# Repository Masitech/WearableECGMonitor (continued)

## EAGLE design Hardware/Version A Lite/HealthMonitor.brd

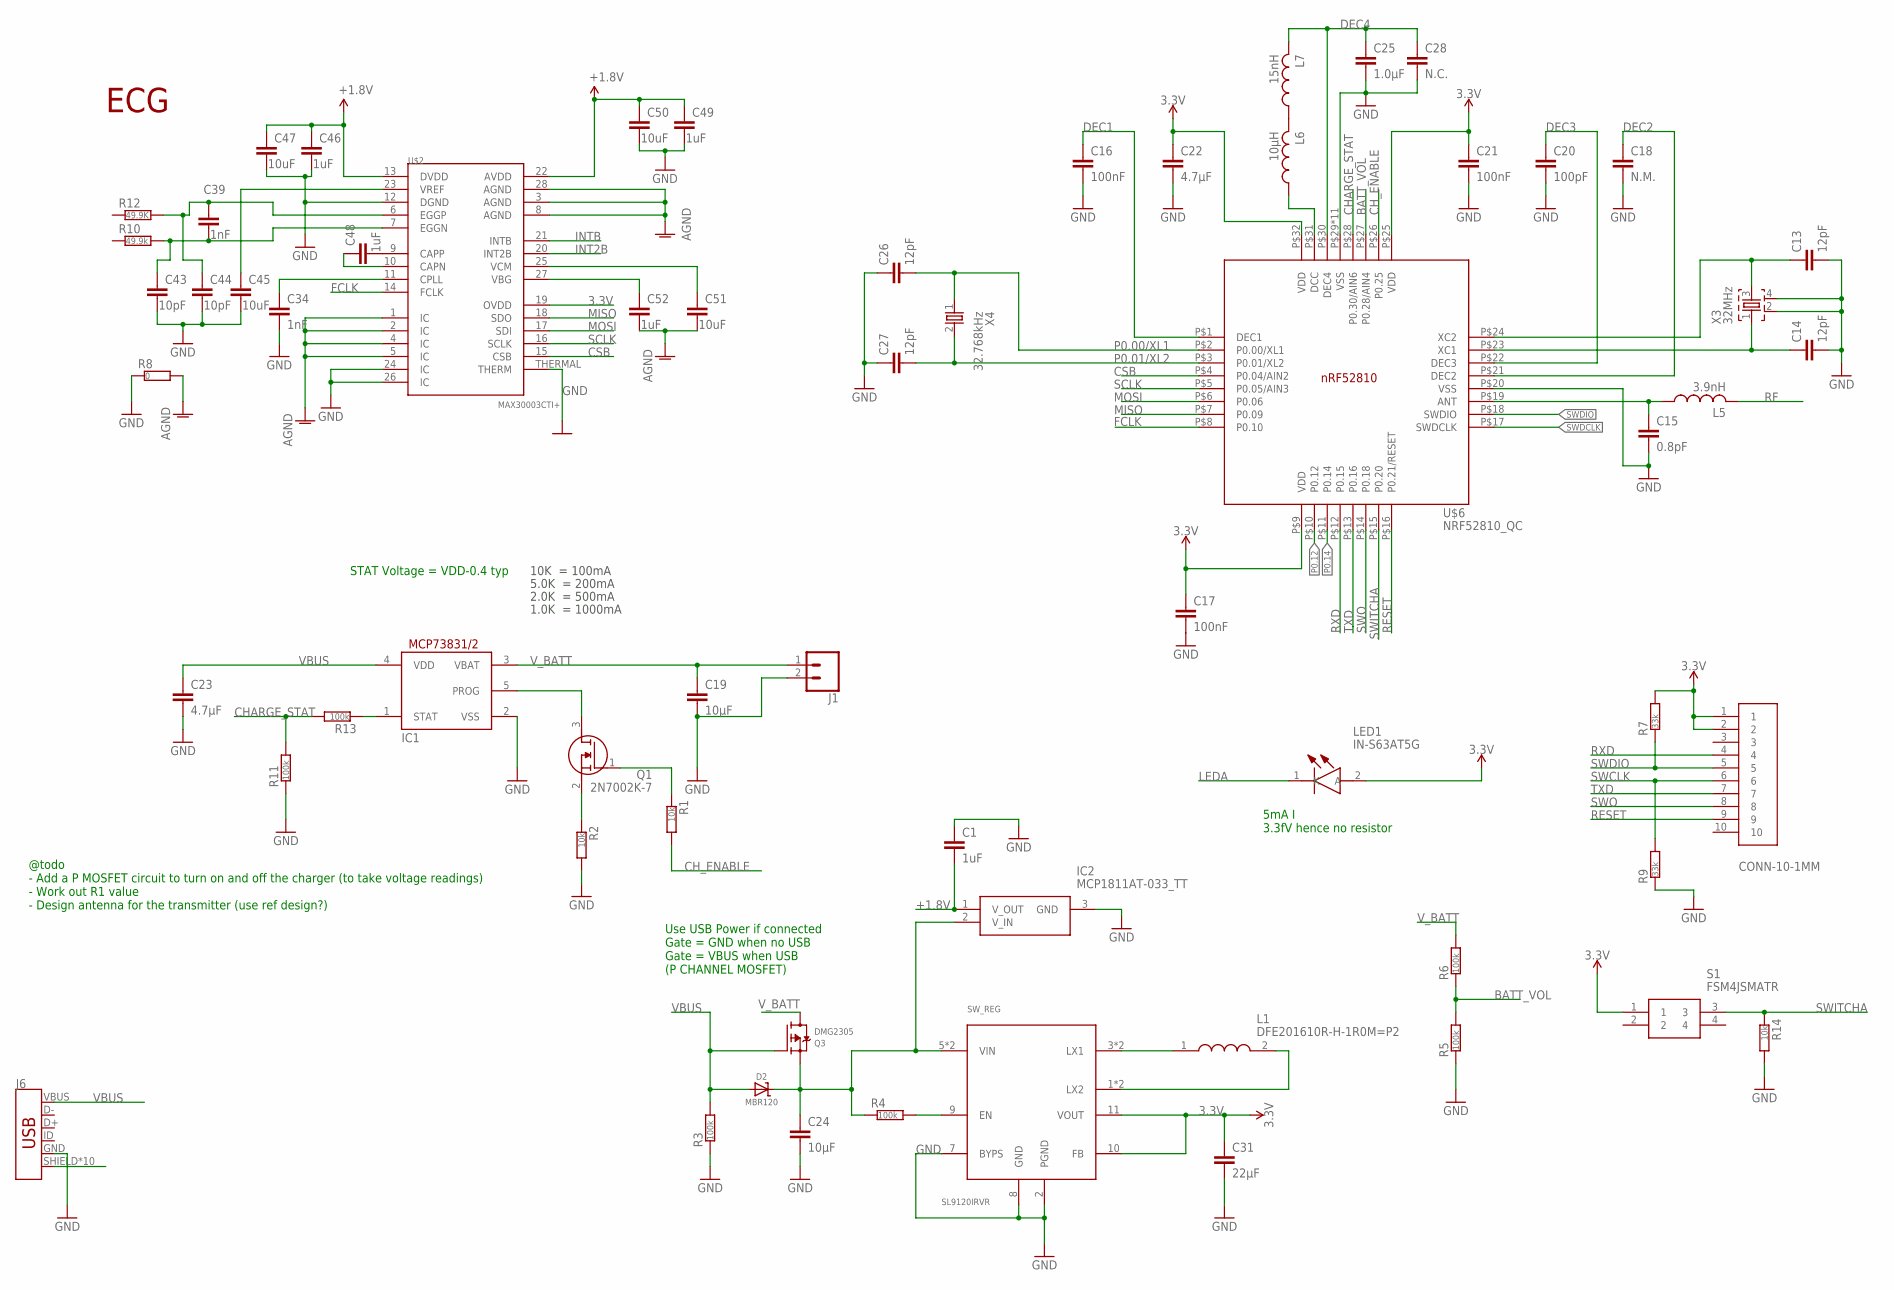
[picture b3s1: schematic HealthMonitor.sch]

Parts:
C1: 1uF; RESC0402_N
C13, C14, C26, C27: 12pF; RESC0402_N
C15: 0.8pF; RESC0402_N
C16, C17, C21: 100nF; RESC0402_N
C18: N.M.; RESC0402_N
C19, C24: 10µF; RESC0603_N
C20: 100pF; RESC0402_N
C22, C23: 4.7µF; RESC0603_N
C25: 1.0µF; RESC0603_N
C28: N.C.; RESC0402_N
C31: 22µF; RESC0603_N
C34: 1nF; C0805
C39: 1nF; RESC0603_N
C43, C44: 10pF; RESC0603_N
C45, C47, C50, C51: 10uF; RESC0603_N
C46, C48, C49, C52: 1uF; RESC0603_N
D2: MBR120; SOD-123
IC1: MCP73831/OT; SOT23-5L
IC2: MCP1811AT-033_TT; SOT95P237X112-3N
J1: CONN_02; 1X02
J6: USB_MICRO-B_HALF_PTH_MILL; USB-MICROB-PTH-MILL
L1: DFE201610R-H-1R0M=P2; INDC2016X100N
L5: 3.9nH; RESC0402_N
L6: 10µH; RESC0603_N
L7: 15nH; RESC0402_N
LED1: IN-S63AT5G; LEDM168X39N
Q1: 2N7002K-7; SOT96P240X100-3N
Q3: DMG2305; SOT23-R
R1, R2, R14: 10k; RESC0402_N
R3, R4, R5, R6, R11, R13: 100k; RESC0402_N
R7, R9: 33k; RESC0402_N
R8: 0; RESC0402_N
R10: 49.9k; RESC0402_N
R12: 49.9K; RESC0402_N
S1: FSM4JSMATR
SW_REG: SL9120IRVR; TQFN-12
U$1: CONN-10-1MM
U$2: MAX30003CTI+; QFN-28
U$6: NRF52810_QC; QFN50P500X500X90-32_N
X3: 32MHz; BT-XTAL_2016_N
X4: 32.768kHz; XTAL_3215_N

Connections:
3.3V: C17.1, C21.1, C22.1, C31.1, LED1.2 (A), R7.2, S1.1, SW_REG.10 (FB), SW_REG.11 (VOUT), U$1.1, U$1.2, U$2.19 (OVDD), U$6.P$9 (VDD), U$6.P$25 (VDD), U$6.P$32 (VDD)
+1.8V: C1.2, C46.1, C47.1, C49.1, C50.1, IC2.1 (V_OUT), U$2.13 (DVDD), U$2.22 (AVDD)
AGND: C51.2, C52.2, R8.2, U$2.1 (IC), U$2.2 (IC), U$2.3 (AGND), U$2.4 (IC), U$2.5 (IC), U$2.8 (AGND), U$2.28 (AGND)
ANT1: C15.1, L5.1, U$6.P$19 (ANT)
BATT_VOL: R5.2, R6.1, U$6.P$27 (P0.28/AIN4)
CHARGE_STAT: R11.2, R13.2, U$6.P$28 (P0.30/AIN6)
CH_ENABLE: R1.2, U$6.P$26 (P0.25)
CSB: U$2.15 (CSB), U$6.P$4 (P0.04/AIN2)
DEC1: C16.1, U$6.P$1 (DEC1)
DEC2: C18.1, U$6.P$21 (DEC2)
DEC3: C20.1, U$6.P$22 (DEC3)
DEC4: C25.1, C28.1, L7.2, U$6.P$30 (DEC4)
ECGN1: C39.2, C43.1, R10.2, U$2.7 (EGGN)
ECGP1: C39.1, C44.1, R12.2, U$2.6 (EGGP)
FCLK: U$2.14 (FCLK), U$6.P$8 (P0.10)
GND: C1.1, C13.2, C14.2, C15.2, C16.2, C17.2, C18.2, C19.2, C20.2, C21.2, C22.2, C23.2, C24.2, C25.2, C26.1, C27.1, C28.2, C31.2, C34.2, C43.2, C44.2, C45.2, C46.2, C47.2, C49.2, C50.2, IC1.2 (VSS), IC2.3 (GND), J1.2, J6.GND, R2.2, R3.1, R5.1, R8.1, R9.1, R11.1, R14.2, SW_REG.2 (PGND), SW_REG.7 (BYPS), SW_REG.8 (GND), U$2.12 (DGND), U$2.24 (IC), U$2.26 (IC), U$2.THERMAL (THERM), U$6.P$20 (VSS), U$6.P$29 (VSS), U$6.P$33 (VSS), U$6.P$34 (VSS), U$6.P$35 (VSS), U$6.P$36 (VSS), U$6.P$37 (VSS), U$6.P$38 (VSS), U$6.P$39 (VSS), U$6.P$40 (VSS), U$6.P$41 (VSS), U$6.P$42 (VSS), X3.2, X3.4
INT2B: U$2.20 (INT2B)
INTB: U$2.21 (INTB)
LEDA: LED1.1 (K)
MISO: U$2.18 (SDO), U$6.P$7 (P0.09)
MOSI: U$2.17 (SDI), U$6.P$6 (P0.06)
unnamed: R4.2, SW_REG.9 (EN)
unnamed: IC1.1 (STAT), R13.1
unnamed: Q1.2 (S), R2.1
unnamed: Q1.1 (G), R1.1
unnamed: L1.1, SW_REG.3 (LX1), SW_REG.4 (LX1)
unnamed: C24.1, D2.C, IC2.2 (V_IN), Q3.2 (S), R4.1, SW_REG.5 (VIN), SW_REG.6 (VIN)
unnamed: IC1.5 (PROG), Q1.3 (D)
unnamed: L1.2, SW_REG.1 (LX2), SW_REG.12 (LX2)
unnamed: C51.1, U$2.25 (VCM)
unnamed: C13.1, U$6.P$24 (XC2), X3.3
unnamed: L6.2, L7.1
unnamed: L6.1, U$6.P$31 (DCC)
unnamed: C34.1, U$2.11 (CPLL)
unnamed: C48.1, U$2.10 (CAPN)
unnamed: C45.1, U$2.23 (VREF)
unnamed: C52.1, U$2.27 (VBG)
unnamed: C48.2, U$2.9 (CAPP)
P0.00/XL1: C26.2, U$6.P$2 (P0.00/XL1), X4.1
P0.01/XL2: C27.2, U$6.P$3 (P0.01/XL2), X4.2
P0.12: U$6.P$10 (P0.12)
P0.14: U$6.P$11 (P0.14)
RESET: U$1.9, U$6.P$16 (P0.21/RESET)
RF: L5.2
RXD: U$1.4, U$6.P$12 (P0.15)
SCLK: U$2.16 (SCLK), U$6.P$5 (P0.05/AIN3)
SHIELD: J6.SHIELD, J6.SHIELD2 (SHIELD), J6.SHIELD3 (SHIELD), J6.SHIELD4 (SHIELD), J6.SHIELD5 (SHIELD), J6.SHIELD6 (SHIELD), J6.SHIELD7 (SHIELD), J6.SHIELD8 (SHIELD), J6.SHIELD9 (SHIELD), J6.SHIELD10 (SHIELD)
SWCLK: R9.2, U$1.6
SWDCLK: U$6.P$17 (SWDCLK)
SWDIO: R7.1, U$1.5, U$6.P$18 (SWDIO)
SWITCHA: R14.1, S1.3, U$6.P$15 (P0.20)
SWO: U$1.8, U$6.P$14 (P0.18)
TXD: U$1.7, U$6.P$13 (P0.16)
VBUS: C23.1, D2.A, IC1.4 (VDD), J6.VBUS, Q3.1 (G), R3.2
V_BATT: C19.1, IC1.3 (VBAT), J1.1, Q3.3 (D), R6.2
X2: C14.1, U$6.P$23 (XC1), X3.1

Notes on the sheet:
10K = 100mA
5.0K = 200mA
2.0K = 500mA
1.0K = 1000mA
Use USB Power if connected Gate = GND when no USB Gate = VBUS when USB (P CHANNEL MOSFET)
ECG
STAT Voltage = VDD-0.4 typ
@todo - Add a P MOSFET circuit to turn on and off the charger (to take voltage readings) - Work out R1 value - Design antenna for the transmitter (use ref design?)
5mA I 3.3fV hence no resistor

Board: 2 copper layers, 63 parts (0 on the bottom side), 49 nets, no tracks yet.

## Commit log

2020-02-20 New Project Base commit: added ecg uart tested
2020-02-28 moved ecg aqua to seperate file / class needs more work
2020-03-07 starting to understand how to use the ble. Its kinda complicated the BLE protocol
2020-03-07 combined custom service + Heart Rate (known service) Reconfigure a known service for ECG ??
2020-03-11 ECG Data reading + UART working on custom board but not BLE, BLE + SPI Read causes a crash am not sure why.
2020-03-11 softdevice file added no changed made to target
2020-03-12 timer 3 interrupt test with led working
2020-03-12 BLE working moved to a seperate file Fix battery measurement adc issue removed unused files
2020-03-12 adc pin changes sdk config to increase resolution
2020-03-14 added ecg service
2020-04-22 cleanup
2020-05-30 Restructure, Hardware files, Documents
    Added: hardware files (all of the versions)
    Specification, Poster, and final report a
2020-08-02 Update README.md
    readme updated
